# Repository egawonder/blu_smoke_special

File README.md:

# Soldering Practice: Never Build This

So, here's a soldering practice board.  Don't actually build it... or at least don't plug it in.  Features:

* Custom foot print for a Molex 8981 (PC power supply 4 pin connector) and SOD-323F (for the surface mount diodes).

* The front has a smiley face in LEDs.

* The back has a 555 astable multivibrator driving a Dickson multiplier.  Unloaded it should produce about 50 V or so.  I found inexpensive 1 uF, 16V caps that will explode nicely (Digikey: 311-1181-1-ND).  If you want to go ahead and use 100V caps (587-1777-1-ND) you can still blow up an electrolytic cap in the banana plug sockets on the right edge of the board.

I have no idea if this actually works.  I mean, it should, maybe.  Anyway, the goal was something to practice soldering on that wouldn't cost too much.  This would be about $10 for three boards at OSHpark.
> The actual board does not need to be electrically functional

Finally, I'm not sure how hard this would be to actually build.  I've never tried to solder SMT components this close together before.  The diodes are a tiny SOD-323F package but the resistors, capacitors and LEDs are larger 1206 components.

## Safety Notice:

Don't plug this in.

## Overview

Schematic:

Layout:

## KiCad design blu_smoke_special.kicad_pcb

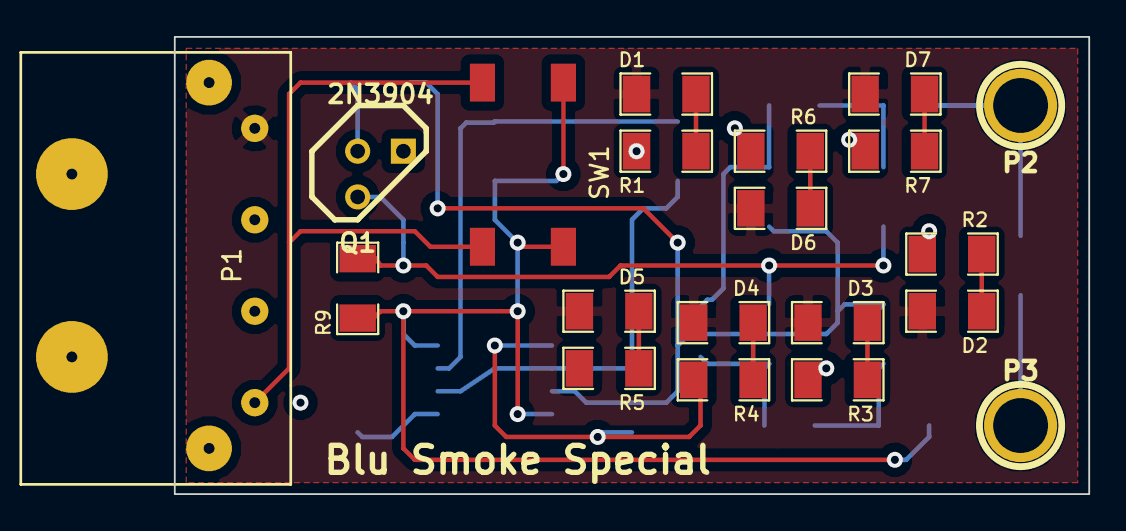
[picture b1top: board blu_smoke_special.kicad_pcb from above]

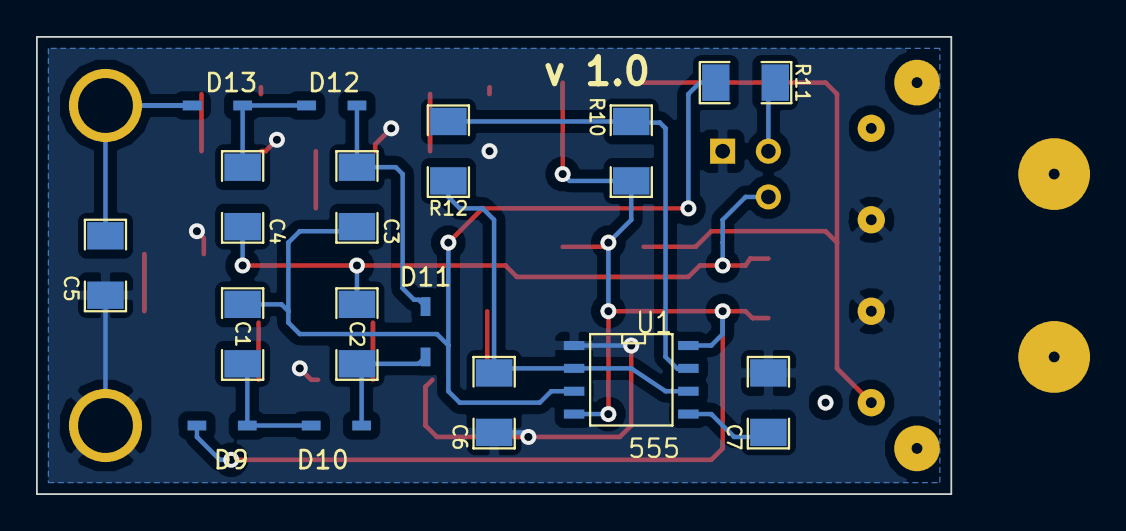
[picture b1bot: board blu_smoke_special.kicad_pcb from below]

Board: 2 copper layers, 50.8 x 25.4 mm, 36 parts (16 on the bottom side), 22 nets.

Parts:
C1, C2, C3, C4, C5: 1u; SM1206
C6: 100n; SM1206
C7: 10n; SM1206
D1, D2, D3, D4, D5, D6, D7: LED; SM1206
D9, D10, D11, D12, D13: 1N4148; SOD-323F
P1: MOLEX-8981
P2, P3: CONN_1; 1pin
Q1: 2N3904; TO92
R1, R2, R3, R4, R5, R6, R7, R10, R11: 470; SM1206
R9, R12: 10K; SM1206
SW1: FSM4JSMA
U1: 555; SO8N

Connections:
/CLK0: C1.2, C3.2, R11.1, U1.3
/CLK1: C2.2, C4.2, Q1.3, R9.2
/HV: C5.1, D13.2, P2.1
/PWR: D9.1, R9.1, R10.1, SW1.3, SW1.4, U1.4, U1.8
GND: C5.2, C6.2, C7.2, P1.2, P1.3, P3.1, Q1.1, R1.2, R2.2, R3.2, R4.2, R5.2, R6.2, R7.2, U1.1
unnamed: D1.2, R1.1
unnamed: D2.2, R2.1
unnamed: D3.2, R3.1
unnamed: D4.2, R4.1
unnamed: D5.2, R5.1
unnamed: D6.2, R6.1
unnamed: D7.2, R7.1
unnamed: Q1.2, R11.2
unnamed: C1.1, D9.2, D10.1
unnamed: C2.1, D10.2, D11.1
unnamed: C3.1, D11.2, D12.1
unnamed: C4.1, D12.2, D13.1
unnamed: P1.1, SW1.1, SW1.2
unnamed: C6.1, R12.2, U1.2, U1.6
unnamed: R10.2, R12.1, U1.7
unnamed: C7.1, U1.5
VCC: D1.1, D2.1, D3.1, D4.1, D5.1, D6.1, D7.1, P1.4

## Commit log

2014-01-28 Initial
2014-01-28 Now with a README
2014-01-28 Now with pictures.
2014-01-28 Images done right. Maybe.
2014-01-29 initial .gitignore file.
2014-01-29 Create blu_smoke_special.lib
    Nothing I do is able to commit this file to the repository. So I've manually created it here.
2014-01-29 Added a switch.
